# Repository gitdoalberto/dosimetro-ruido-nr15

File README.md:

# Dosímetro de Ruído NR 15

Projeto desenvolvido como Eetapa de Capacitação Profissional - Embarcatech.

Dosímetro de Ruído NR 15 - para a medição e monitoramento de níveis de ruído, visando atender aos requisitos da Norma Regulamentadora NR 15.

## Apresentação do Projeto

Um dosímetro de ruído é um dispositivo usado para medir a exposição ao ruído ao longo do tempo, geralmente em ambientes de trabalho. Ele é essencial para a segurança ocupacional, pois ajuda a determinar se um trabalhador está sendo exposto a níveis de som que podem causar danos auditivos.

Este projeto visa desenvolver um dosímetro de ruído portátil que atenda às normas da NR-15, que regulamenta a exposição dos trabalhadores a níveis de ruído ocupacional. O dispositivo será capaz de medir, em tempo real, os níveis de pressão sonora e calcular a dose de ruído diária, garantindo a segurança e saúde dos trabalhadores em ambientes industriais.

## Objetivos do Projeto

- Desenvolver um dispositivo portátil e de baixo custo para medição de ruído ocupacional.
- Garantir que o dispositivo atenda aos requisitos da NR-15, fornecendo dados precisos sobre a exposição ao ruído.
- Facilitar a monitoração contínua e automática dos níveis de ruído em ambientes de trabalho.
- Fornecer alertas sonoros e visuais quando os limites de exposição forem ultrapassados.

## Principais Requisitos
- **Precisão:** O dispositivo deve medir níveis de ruído com precisão de ±1 dB.
- **Portabilidade:** O dosímetro deve ser leve e compacto, permitindo que o trabalhador o carregue consigo durante a jornada de trabalho.
- **Autonomia:** Bateria com duração mínima de 8 horas.
- **Interface Amigável:** Display LCD ou LED para mostrar os níveis de ruído em tempo real e a dose acumulada.
- **Conformidade:** O dispositivo deve ser capaz de calcular a dose de ruído de acordo com os limites estabelecidos pela NR-15.
- **Durabilidade:** Resistente a poeira e água, atendendo ao padrão IP54.

## Descrição do Funcionamento
O dosímetro de ruído portátil funcionará da seguinte maneira:
- **Captação do Som:** Um microfone de alta sensibilidade captará os sons ambientais.
- **Processamento do Sinal:** O sinal será processado por um microcontrolador que calculará o nível de pressão sonora em dB(A).
- **Cálculo da Dose de Ruído:** O microcontrolador calculará a dose de ruído acumulada ao longo do tempo, comparando-a com os limites da NR-15.
- **Exibição dos Dados:** Os dados serão exibidos em um display LCD, mostrando o nível de ruído atual, a dose acumulada e o tempo restante de exposição segura.
- **Alertas:** Se os limites de exposição forem ultrapassados, o dispositivo emitirá alertas sonoros e visuais.
- **Armazenamento de Dados:** O dispositivo poderá armazenar os dados coletados para posterior análise.

## Justificativa
A exposição excessiva ao ruído em ambientes industriais é uma das principais causas de perda auditiva ocupacional. A NR-15 regulamenta limites de tolerância ao ruído para garantir a segurança dos trabalhadores. No entanto, muitas empresas não possuem meios eficientes para monitorar e gerenciar a exposição ao som. O desenvolvimento deste dosímetro possibilita a prevenção de doenças ocupacionais, contribuindo para um ambiente de trabalho mais seguro.

## Originalidade

Existem diversos dosímetros comerciais no mercado, como os fabricados pela 3M e Bruel & Kjaer, que são eficientes, mas muitas
vezes de alto custo. Este projeto propõe um dispositivo mais acessível, com funcionalidades personalizadas e integração com
sistemas de monitoramento real. Além disso, sua capacidade de exportação de dados para análise computacional o torna uma
ferramenta valiosa para gestores de segurança do trabalho.

## Conclusão
O Dosímetro de Ruído Portátil NR-15 é uma solução inovadora e necessária para a monitoração contínua da exposição ao ruído
ocupacional. Com sua portabilidade, precisão e conformidade com as normas regulamentadoras, este dispositivo tem o potencial
de melhorar significativamente a segurança e saúde dos trabalhadores em ambientes industriais.

## Hardware Utilizado

- **Microcontrolador:** RP2040
- **Microfone:** Microfone com Amplificador MAX4466
- **Conversor ADC:** RP2040
- **Display:  SSD1306, 128x64px, I2C** 
- **LED RGB:** 3 cores
- **Buzzer:** Buzzer piezoelétrico
- **Componentes Adicionais:** [capacitores, resistores, conectores 2 pin e micro-usb]

## Software e Bibliotecas

- **Ambiente de Desenvolvimento:** Visual Code e Pico SDK
- **Linguagem de Programação:** Linguagem C
- **Bibliotecas Utilizadas:** 
  - [<stdio.h>, <math.h>, <string.h, "pico/stdlib.h", "hardware/adc.h", "hardware/dma.h", "hardware/gpio.h", "hardware/pwm.h", "hardware/pio.h" e "inc/ssd1306.h"]

## Uso do Firmware/Software:
Caso queiara testar o firmware basta copiar o arquivo **dosimetro.uf2** para seu dispositivo.

 **Ou Clone o Repositório:**
   ```bash
   git clone https://github.com/gitdoalberto/dosimetro-ruido-nr15.git

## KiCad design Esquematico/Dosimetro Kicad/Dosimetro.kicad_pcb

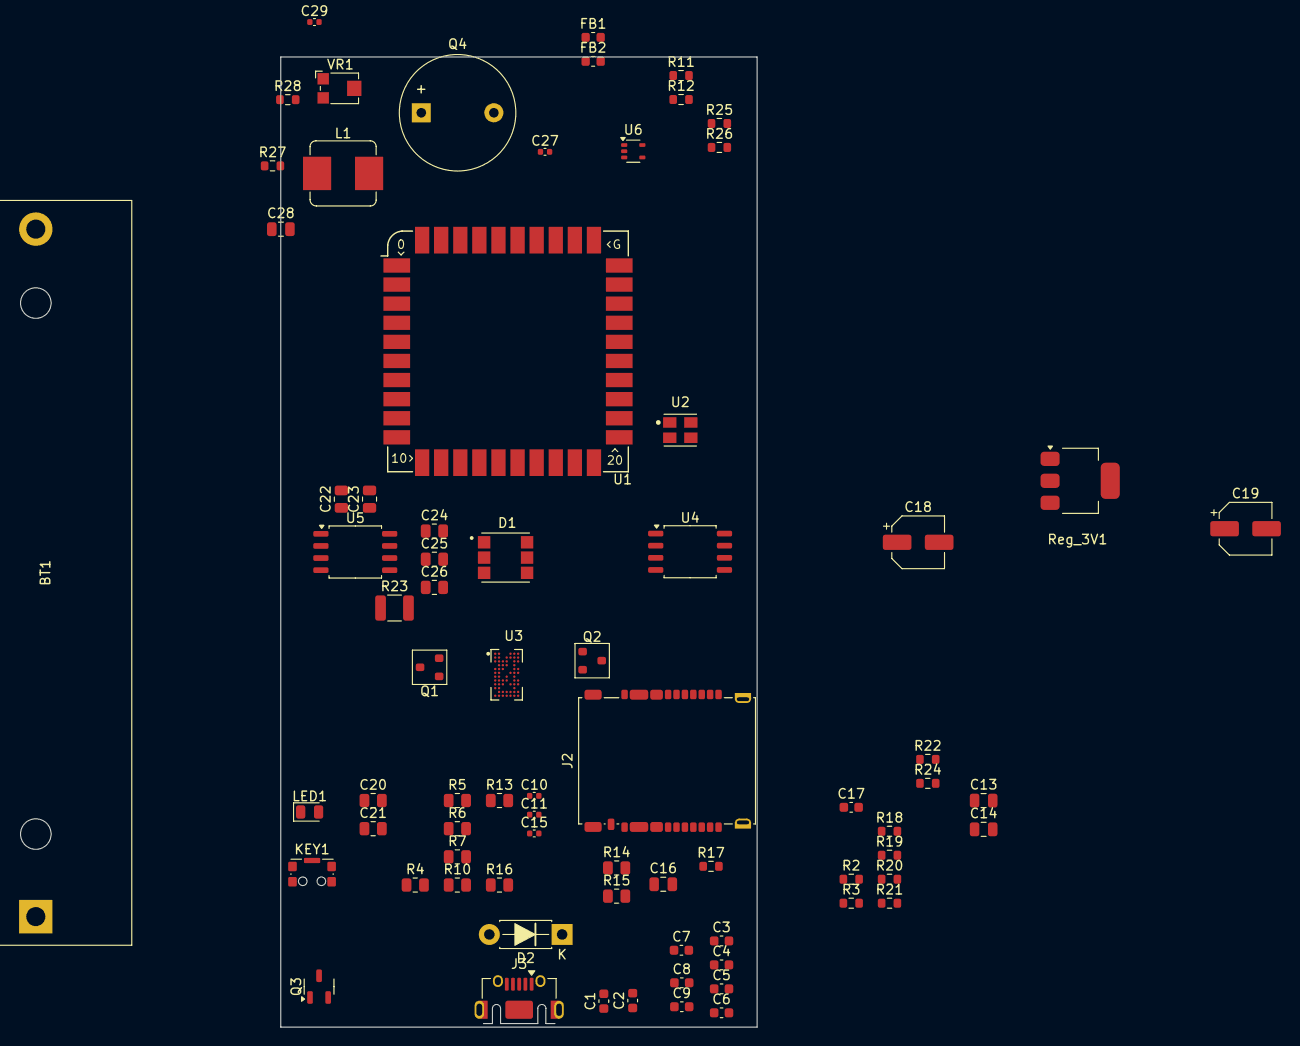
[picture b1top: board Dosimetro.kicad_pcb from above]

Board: 2 copper layers, 49.9 x 101.6 mm, 75 parts (0 on the bottom side), 44 nets, no tracks yet.

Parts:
BT1: Battery_Cell; BatteryHolder_MPD_BH-18650-PC2
C1, C2, C3, C4, C5, C6, C7, C8, C9, C17: 100n; C_0603_1608Metric
C10, C11: 1u; C_0402_1005Metric
C13, C14: 15p; C_0805_2012Metric
C15: 0.1µF; C_0402_1005Metric
C16: 10u; C_0805_2012Metric
C18, C19: C_Polarized_Small; CP_Elec_5x5.9
C20, C21, C22, C23: 10u; R_0805_2012Metric
C24, C25, C26: 22u; R_0805_2012Metric
C27: 0.01uF; C_0402_1005Metric
C28: 10uF; C_0805_2012Metric
C29: 100pF; C_0402_1005Metric
D1: LTST-G563ZEGBW; LED_LTST-G563ZEGBW
D2: 1N5819; D_DO-41_SOD81_P7.62mm_Horizontal
FB1, FB2: FERRITE; L_0603_1608Metric
J2: Micro_SD_Card_Det2; SD-SIM_microSD-microSIM_Molex_104168-1620
J3: USB_B_Micro; USB_Micro-AB_Molex_47590-0001
KEY1: TS24CA; SW_SPST_CK_KMS2xxGP
L1: 1uH; L_Bourns_SRP7028A_7.3x6.6mm
LED1: PWR; LED_0805_2012Metric
Q1, Q2: BC817; SOT-23
Q3: DMG2305UX-13; SOT-23-3
Q4: CMA-4544PF-W; Buzzer_12x9.5RM7.6
R2, R3: 27.4; R_0603_1608Metric
R4, R6, R7: 220; R_0805_2012Metric
R5, R16: 1k; R_0805_2012Metric
R10, R13: 330; R_0805_2012Metric
R11, R25, R27: 1K; R_0603_1608Metric
R12, R26: 1M; R_0603_1608Metric
R14, R15: 10k; R_0805_2012Metric
R17: DNF; R_0603_1608Metric
R18: 0R; R_0603_1608Metric
R19, R24: 10k; R_0603_1608Metric
R20, R21: 2R; R_0603_1608Metric
R22: 20R; R_0603_1608Metric
R23: 100R; R_1210_3225Metric
R28: 22K; R_0603_1608Metric
Reg_3V1: 3.3v_smd; SOT-223
U1: RP2040; RP2xxx_Stamp_SMD
U2: ABM8-272-T3
U3: CYW43439KUBGT; BGA63N40P7X12_287X487X55N
U4: W25Q128JVS; SOIC-8_5.23x5.23mm_P1.27mm
U5: IP5306; SOP-8_5.28x5.23mm_P1.27mm
U6: MAX4466EXK+T; SOT-353_SC-70-5
VR1: TC33X-2-104E (100K); Potentiometer_Bourns_TC33X_Vertical

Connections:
+1V1: C1.1, C2.1, C10.1, U1.23 (DVDD)
+3.3V: C3.1, C4.1, C5.1, C6.1, C7.1, C8.1, C16.1, C19.1, FB1.2, R14.2, R15.2, Reg_3V1.2 (VO), Reg_3V1.4 (VO)
+3V3: C17.1, U4.8 (VCC)
/GPI017: R17.2, U1.32 (GPIO21)
/GPIO010: R10.1, U1.13 (GPIO10)
/GPIO011: D1.2, U1.14 (GPIO11)
/GPIO012: D1.3, U1.15 (GPIO12)
/GPIO013: D1.1, U1.16 (GPIO13)
/GPIO028: C29.1, VR1.1 (A), VR1.2 (S)
AVCC: FB1.1, R11.2, R12.2, U6.5 (VCC)
D+: J3.3 (D+), R2.2
D-: J3.2 (D-), R3.2
GND: BT1.2 (-), C1.2, C2.2, C3.2, C4.2, C5.2, C6.2, C7.2, C8.2, C9.2, C10.2, C11.1, C11.2, C13.1, C14.1, C16.2, C17.2, C18.2, C19.2, C20.2, C21.2, C22.2, C23.2, C24.2, C25.2, C26.2, J3.5 (GND), J3.6 (Shield), Q1.2 (E), Q2.2 (E), R4.1, R6.1, R7.1, R17.1, R23.2, Reg_3V1.1 (ADJ), U1.1 (IOVDD), U1.10 (IOVDD), U1.22 (IOVDD), U1.33 (IOVDD), U2.2, U2.4, U3.B1 (BT_DEV_WAKE), U4.4 (GND)
GNDA: C15.2, C28.2, FB2.1, Q4.2 (+), R26.1, U6.2 (GND)
GNDREF: FB2.2, R19.2
unnamed: C14.2, R5.1, U2.3
unnamed: C15.1, R11.1, R25.2
unnamed: C20.1, R20.1
unnamed: C27.1, Q4.1 (-), R25.1
unnamed: C27.2, R12.1, R26.2, U6.1 (IN+)
unnamed: C28.1, R27.1
unnamed: C29.2, R27.2, R28.1, U6.3 (IN-)
unnamed: D1.4, R4.2
unnamed: D1.5, R6.2
unnamed: D1.6, R7.2
unnamed: D2.2 (A), J3.1 (VBUS)
unnamed: KEY1.1, R24.1
unnamed: LED1.1 (A), R22.1
unnamed: Q1.1 (B), R10.2
unnamed: Q2.1 (B), R13.2
unnamed: C24.1, C25.1, C26.1, Q3.3 (D), R23.1, U5.8 (VOUT)
unnamed: Q3.1 (G), R18.2
unnamed: C13.2, U1.20 (XIN), U2.1
unnamed: R5.2, U1.21 (XOUT)
unnamed: R16.1, U4.1 (~CS)
unnamed: C23.1, R21.1, U5.6 (BAT)
unnamed: R22.2, R24.2, U5.5 (KEY)
unnamed: L1.1, U5.7 (SW)
unnamed: R28.2, VR1.3 (E)
VBUS: C21.1, D2.1 (K), R18.1, R19.1, R20.2, U5.1 (VIN)
VSYS: C18.1, Q3.2 (S), Reg_3V1.3 (VI)
V_BAT +: BT1.1 (+), C22.1, L1.2, R21.2
WL_CMD: U3.L6 (SDIO_CMD), U3.L7 (SDIO_DATA_2)
WL_ON: U3.E6 (BT_REG_ON), U3.G6 (WL_REG_ON)

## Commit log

2025-02-23 Remove repositório interno e adiciona Software/dosimetro
2025-02-23 arquivos
2025-02-23 Binario UF2
